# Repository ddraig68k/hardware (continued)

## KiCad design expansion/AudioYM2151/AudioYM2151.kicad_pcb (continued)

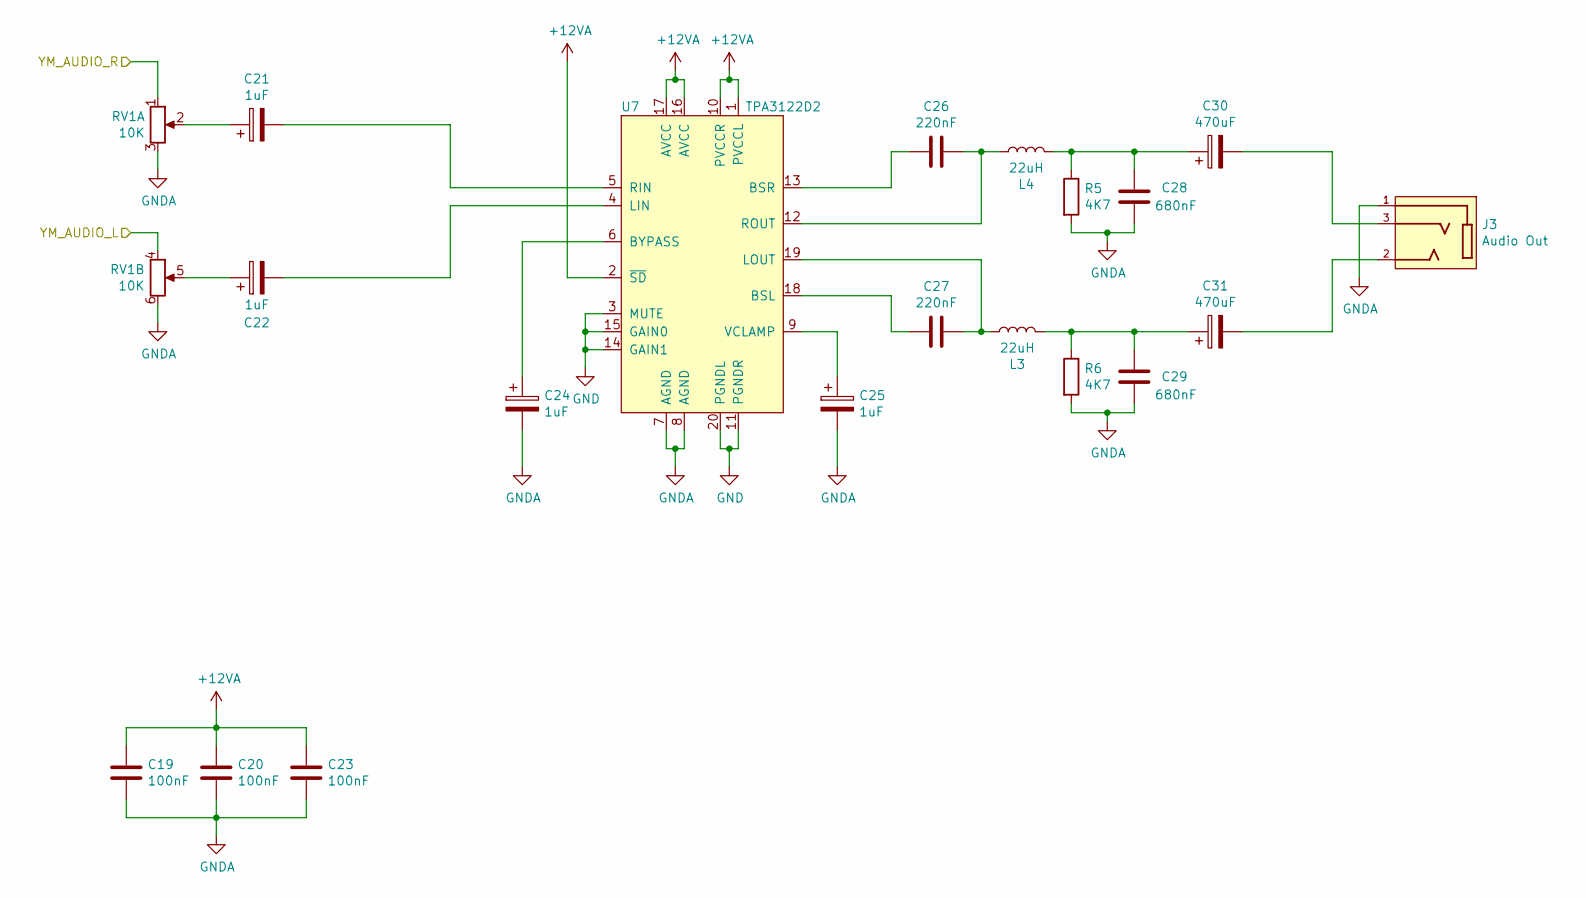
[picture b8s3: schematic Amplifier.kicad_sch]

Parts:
C19, C20, C23: 100nF; C_Disc_D5.0mm_W2.5mm_P2.50mm
C21, C22, C24, C25: 1uF; CP_Radial_D5.0mm_P2.50mm
C26, C27: 220nF; C_Disc_D5.0mm_W2.5mm_P2.50mm
C28, C29: 680nF; C_Disc_D5.0mm_W2.5mm_P2.50mm
C30, C31: 470uF; CP_Radial_D10.0mm_P5.00mm
J3: Audio Out; SWITCHCRAFT_35RAPC2BHN2; PARTREV L
L3, L4: 22uH; L_Radial_D8.7mm_P5.00mm_Fastron_07HCP
R5, R6: 4K7; R_Axial_DIN0207_L6.3mm_D2.5mm_P10.16mm_Horizontal
RV1: 10K; Potentiometer_Alps_RK163_Dual_Horizontal
U7: TPA3122D2; DIP-20_W7.62mm_Socket

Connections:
+12VA: C19.1, C20.1, C23.1, U7.1 (PVCCL), U7.2 (~SD), U7.10 (PVCCR), U7.16 (AVCC), U7.17 (AVCC); also elsewhere on the board
/Amplifier/YM_AUDIO_L: RV1.4; also elsewhere on the board
/Amplifier/YM_AUDIO_R: RV1.1; also elsewhere on the board
GND: U7.3 (MUTE), U7.11 (PGNDR), U7.14 (GAIN1), U7.15 (GAIN0), U7.20 (PGNDL); also elsewhere on the board
GNDA: C19.2, C20.2, C23.2, C24.2, C25.2, C28.1, C29.1, J3.1, R5.2, R6.2, RV1.3, RV1.6, U7.7 (AGND), U7.8 (AGND); also elsewhere on the board
unnamed: C21.1, RV1.2
unnamed: C22.1, RV1.5
unnamed: C28.2, C30.1, L4.2, R5.1
unnamed: C29.2, C31.1, L3.2, R6.1
unnamed: C30.2, J3.3
unnamed: C31.2, J3.2
unnamed: C27.2, U7.18 (BSL)
unnamed: C26.2, U7.13 (BSR)
unnamed: C24.1, U7.6 (BYPASS)
unnamed: C22.2, U7.4 (LIN)
unnamed: C27.1, L3.1, U7.19 (LOUT)
unnamed: C21.2, U7.5 (RIN)
unnamed: C26.1, L4.1, U7.12 (ROUT)
unnamed: C25.1, U7.9 (VCLAMP)

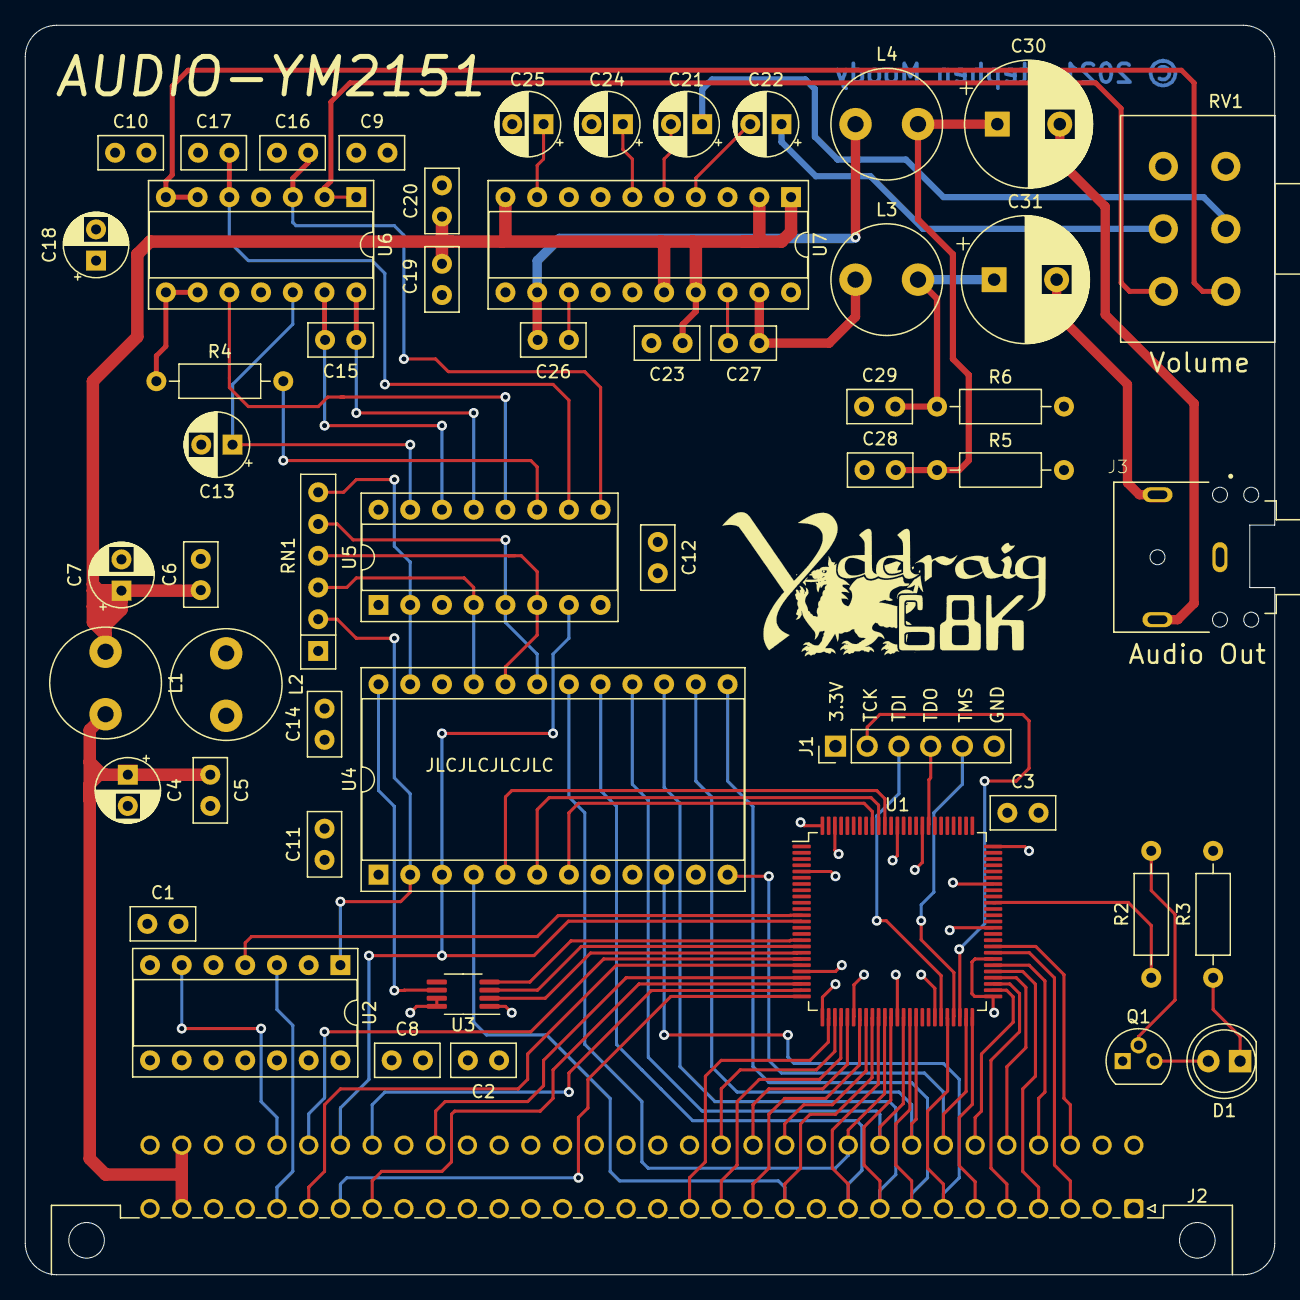
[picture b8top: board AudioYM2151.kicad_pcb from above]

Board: 4 copper layers, 100.0 x 100.0 mm, 54 parts (0 on the bottom side), 83 nets.

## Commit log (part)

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2021-06-23 Added V9990 IC
2021-06-25 Working on V9990 Gfx card
2021-06-25 Added XCA2075M to library
2021-06-25 More additions to the V9990
2021-06-27 Updated YM2612
2021-06-27 Added Eth8019 and updated page description for all projects
2021-06-27 Added extra capacitors to RTL8019
2021-06-27 Started work on V9990 PCB layout
2021-06-29 Updated Mini Din footprints
2021-06-30 Started working on V9958 PCB layout
2021-07-02 Working on YM2612 layout
2021-07-03 Removed V9990 schematic
2021-07-03 Some YM2612 layout changes
2021-07-03 YM2612 layout done
2021-07-05 Done some work on the 68030 design
2021-07-05 Work done on 68K expansion boards
2021-07-06 Removed MSM ADPCM chip from YM2151 board
2021-07-07 Re-started layout on YM2151 board
2021-07-12 Update ddraig logo library symbols
2021-07-13 Started routing Ethernet board
2021-07-13 Finished layout of RTL8019 Ethernet board
2021-07-14 Tidying up logos and copyright
2021-07-22 Re-added V9958 project
2021-07-23 Tiday up of V9958 pcb
2021-07-23 Updated 3D model path reference
2021-07-25 Added joystick board project
2021-07-26 Added PCB for Joypad controller
2021-07-26 Added JTAG labeling on Joypad board
2021-07-27 Changed PCB layout to 100x100 baord
2021-07-28 Updated Trnsistor to SMD part
2021-07-28 Updated v9990 schematic to use SMD parts
2021-07-28 Corrected resistor value from 2K81 -> 2K61
2021-07-29 V9990 part placement done
2021-07-29 Updated PDF schematics for all boards
2021-07-30 Generated gerber files
2021-08-14 Updated incorrectly labeled component
2021-08-18 Completed PCB layout
2021-08-21 Started working on FPGA card design
2021-08-21 More progress on VGA card design
2021-08-21 Started PCB layout
2021-08-23 Improvements on bus wiring pinouts
2021-08-24 Trying to figure out SRAM layout
2021-08-24 Fix for POWER and RESET switches
2021-08-24 Working on the pinning of the FPGA pins
2021-08-25 Updated labeling on Y ddraig board
2021-08-25 Added CPLD code for the Eth8019 card
2021-08-25 Some updates to the VGA FPGA pinout
2021-08-25 Additional work to FPGA VGA schematic
2021-08-26 More work on VGA card
2021-08-28 Changed yddraig68k CPLD macrocells to low power
2021-08-29 Working on YM2203 component
2021-08-29 Added a few extra footprints
2021-08-29 Some minor changes to the FPGA video board
2021-08-29 More work done on the 68030 and 6809 boards
2021-08-29 FIx for 74HCT74 power symbol connections
2021-08-31 Renamed yddraig68k to yddraig
2021-08-31 Updated Readme files
2021-08-31 Some more changes to the 030 and 6809 designs
2021-08-31 Started adding W65C22
2021-09-01 Completed W65C22 part
2021-09-01 Add project names
2021-09-01 changed IC
2021-09-02 Added readme for 6809 board
2021-09-03 Minor changes to DRAM page
2021-09-05 Added RYC8220 to library
2021-09-05 Added IO sheet
2021-09-06 Joypad board, tidied up PCB a little
2021-09-06 TMS9918 - Updated crystal capacitor values to 22pF
2021-09-07 yddraig09 added sd card and iec interfaces
2021-09-07 Updated IO on some of the child sheets
2021-09-08 Buffer for data bus added
2021-09-08 yddraig030 - Updated expansion slot schematics
2021-09-08 Y Ddraig PCB update
2021-09-10 More work y ddraig 030
2021-09-10 More work on yddraig 030
2021-09-11 More 030 changes
2021-09-11 More work on 030 board
2021-09-14 Some work on main ddraig030 sheet
2021-09-14 Changed coaxial connector
2021-09-14 Y Ddraig CPLD code update for PIT
2021-09-14 Yddraig09 Added keyboard page to schematic
2021-09-15 Added some parts for the keyboard controller
2021-09-16 Small updates to keyboard and RAM pages
2021-09-16 More work on 6809 board
2021-09-17 More 6809 changes
2021-09-17 Some tidying up of 6809 project
2021-09-18 ddraig09: Added decode logic and expansion slot
2021-09-18 ddraig09: initial design done
    Need to be reviewed and decode on additional uses for IO but passed DRC
2021-09-19 Asssigned part footprints to most of schematic
2021-09-19 ddraig09: all footprints assigned
2021-09-22 Added initial 6809 board layout design
2021-09-22 Updated the regulator footprint
2021-09-23 Changes to 6809 pcb layout
2021-09-24 Expermienting with 6809 RAM bank logic
2021-09-24 Started removing 6809 sdcard interface
2021-09-26 6809: Restored SD card schematic
2021-09-29 Working on the PCB layout
2021-10-02 ddraig030: Started changing the address decode logic
2021-10-03 ddraig09: Started routing on new layout
2021-10-04 small change
2021-10-06 ddraig030: Some changes to address decoding logic
2021-10-06 ddraig030: Some additional changes to address decoding logic
2021-10-08 Added USB and 72-pin SIMM sockets
2021-10-08 ddraig030: more changes as footprints assigned
2021-10-09 ddraig09: fix for the TSC pin
2021-10-27 Created project for YM2151 CPLD code
2021-10-29 Some basic code for the YM2151 CPLD
2021-11-10 AudioYM2151: Almost done on the CPLD logic, still not working 100%
2021-12-01 yddraig: Updated power circuit to use through hole parts rather than SMD
2021-12-01 yddraig: Moves the DTACK signal from the IRQ line on expansion slot 3
    Close #2
2021-12-01 ym2151: Update to the SPI clock handling code
2021-12-04 ym2151: Added constraints file for the CPLD code
2021-12-05 ym2151: Minor changes and fixed warnings in code
2021-12-06 ym2151: CPLD spi writing seems to be working now
2021-12-06 yddraig030: changed expansion bus and RAM and ROM to 16 bit
2021-12-08 ym2151 CPLD code working correctly
2021-12-10 CPLD for YM2151 made write only, initial YM2612 code
2021-12-13 Added initial V9958 code
2021-12-29 Updated tested cards in readme
2021-12-29 Removed the ddraig030WIP folder
2021-12-30 Updated to KiCAD6
2021-12-30 Spelling fix
2022-01-17 yddraig030: some small changes to the schematic
2022-01-17 Started design for a USB host board
2022-01-17 GfxV9990: Updated CPLD code for the device
2022-02-02 GfxV9990: Changes to the CPLD read and write timings
2022-02-05 JoypadController: Added initial CPLD code
2022-04-08 Updating the YM2151 CPLD codew
2022-04-08 Updated Joypad CPLD to use correct expansion ID
2022-05-07 Updated Joystick controller CPLD code
2022-05-29 Fix for CXA PAL issue and more
2022-06-03 Updated library to new format
2022-06-03 More progress on Spartan-3 FPGA board
2022-06-04 Part placement on video card
2022-06-06 Latest changes to GfxFPGAS3
2022-06-08 Reworking FPGA VGA Card Pinout
2022-06-23 Fix clock frequency setting for YM2151
2022-06-23 More work on the 030 board
2022-06-26 Updated 030 design files
2022-07-29 Added labels to VDP FPGA card
2022-07-29 More changes to the 030 board
2022-07-30 ddraig030 schematic done
2022-07-31 Small changes to 030 design
2022-08-04 More changes in yddraig030 layout
2022-08-10 yddraig030: board changed, ready for footprint assignment
2022-08-10 Some small PCB change?
2022-08-12 Working on PCB layout
2022-08-17 Some more changes to SMD version
2022-08-17 Minor layout changes
2022-08-17 GfxFPGAS3: Added gerber files
2022-08-29 030 board, expansion cards fully routed
2022-08-31 Additional routing don CPU
2022-09-01 Additional routing
2022-09-04 Fix for BUSENABLE not placable on FPGA
2022-09-04 More routing on the 030 board
2022-09-06 More routing
2022-09-08 Board fully routed
2022-09-09 Maybe a final board design?
2022-09-10 Updated silscreen for board
2022-09-10 Updated Yddraig030 schematic
2022-09-10 Updated yddraig09 silkscreen
2022-12-02 Updated readme file
2022-12-02 Added YM2151 picture
2022-12-02 Added y Ddraig image
2022-12-02 Added README to the YM2151
2022-12-02 Updated YM2151 YouTube link
2022-12-02 Mod to YM2151 README
2022-12-03 Added TMS9918 Images
2022-12-03 Added readme for the TMS9918
2022-12-03 Added images for the V9958
2022-12-03 Added README for V9958
2022-12-03 Added README for the V9990
2023-01-14 Updated Logic ICs to specific SMD parts and footprints in schematic
2023-01-14 Updated yddraig030 PCB layout to match schematic changes
2023-01-27 Considering adding second sound channel to 6809 board
2023-01-28 Changes to 030 design completed
2023-02-04 Small updates to 6809 and 030 board, remove old files
2023-02-04 Updated 030 and 6809 gerbers
2023-02-05 Changed a footprint and gerbers for yddraig030
2023-02-06 Updated gerbers with missing bottom solder mask
2023-02-25 Updated 6809 readme
2023-05-20 Updated 68030 CPLD decode logic
2023-07-24 Starting to work on some new boards
2023-07-24 Some updates
2023-09-09 Initial version of a Dual SID audio card
2023-09-09 Removed 74LS125 from schematic
2023-09-16 Changed oscillator frequency on the keyboard controller
2023-09-16 Wotking on SID audio PCB placement
2023-09-17 Working on SID PCB layout
2023-09-18 Audio SID board routed
2023-10-23 Added some labels to Audio SID board
2023-11-15 Working on some new GFX ideas
2023-11-22 Added Spartan-7 FPGA
2023-11-22 Working on HDMI board
2023-11-28 More work on the HDMI board
2024-01-05 Added gerbers to SID board
2024-01-12 Updated AudioSID CPLD code
2024-01-20 FDC updated to KiCAD 7
2024-01-20 All projects updated to KiCAD 7 format files
2024-01-20 Added WIP Boards
2024-01-24 Fixed STACK logic
2024-01-25 Fix for SID Audio VHDL
2024-02-05 Modified volume control on YM2151 card
2024-02-08 Working on CPU schematic
2024-02-09 more work on 68008
2024-02-09 more work on new audio card
2024-02-11 Updated YM2151 Board
2024-02-17 Fix the serial port on yddraig09
2024-02-17 More changes to YM2151V2
2024-02-17 Addon card for yddraig09 to fix bad serial design
2024-02-17 Completed YM2151V2 schematic
2024-02-17 Updated headphone socket cad
2024-02-24 Removed on of the MSM ICs from YM2161V2 design
2024-02-25 Starting pcb layout
2024-02-26 Added more layout changes to new YM2151 board
2024-02-27 Added some CAD models
2024-02-27 Updated 3d models
2024-02-27 Working on footprint positions
2024-02-29 Finished YM2151 audio layout
2024-03-02 Some YM2151 updates
2024-03-02 Started layout of YM2151
2024-03-08 YM2151 board layout progress
2024-03-09 Finished YM2151 board layout
2024-03-25 Initial dram controller code
2024-03-25 DRAM controller compiles
2024-03-29 Updated 030 dram contoller code
2024-03-30 Added some labels to YM2151 V2 board
2024-03-30 Updated DRAM test bench
2024-05-16 Some changes to YM2151 V2 Board
2024-05-17 Updated YM2151V2 crystal capacitors to 15pf
2024-05-17 Latest changes
2024-05-17 Updated libraries with the latest additions
2024-05-17 ddraig030: Updated some 3d models on the PCB layout
2024-05-17 yddraig: Updated some 3d models on the PCB layout and altered CPLD DRAM timing
2024-05-17 V9990 card, restored some timing from the V9990 CPLD
2024-05-17 AudioSID: Fix to CPLD decode logic
2024-05-17 Fixed some AudioYM2151V2 DRC issues
2024-05-17 Added additional user LED to YM2151V2 design
2024-05-24 Looking at working on new FPGA video card
2024-05-24 Genereted YM2151V2 gerber files
2024-05-25 Pinout done one VGA card
2024-05-25 intitial FPGA routing done
2024-05-26 Added 32 bit version of VGA card
2024-06-01 Fixed DTACK signal generation
2024-06-05 V9990 WIP
2024-06-06 Some changed to track limits for FPGA board
2024-06-07 Updating YM2151V2 readme
2024-06-07 Fixed the DUART on the 6809
2024-06-12 Saved in V8 format
2024-06-24 Working on VGA baord layout
2024-06-24 VGA board v2 routing done
2024-07-11 WOrking on FPGA VGA board
2024-07-12 WOrking on VGA card
2024-07-13 Finished FPGA board layout
2024-07-19 Updated V9990 schematic
2024-07-19 Some changes
2024-07-21 Changing the yddraig09 project
2024-07-27 6809 board changes
2024-07-27 Gfx FPGA and V9990 gerber changes
2024-07-28 Changes to yddraig09
2024-07-30 More changes
2024-07-31 Changed RTC
2024-08-03 Changed RTC and board layout
2024-08-04 Updated V9990 and FPGA board
2024-08-14 BOard changes
2024-08-28 Added gerber files got VGA and V9990 cards
2024-09-09 Updated Audio socket on V9990 board
2024-10-01 V9990 and VGA Minor updates and new gerbers
2024-10-13 Updated 030 address decode logic
2024-10-17 Changing v9990 board
2024-10-19 Changes to the HDMI board
2025-01-11 Repository clean up, removed untested projects
    Updated files to latest KiCAD version
    Removed untested 68030 design files
    Removed 6809 board, several design flaws
    Removed untested expansion boards
2025-01-11 Update README.md
    Removed KiCAD 6 reference
2025-01-16 Updated MC68681 symbol
2025-10-01 Added the design files for GfxvGA card
2026-02-27 Merged 2 conflicting branches
2026-04-16 Added second clock out to CPLD
2026-04-16 Fixed incorrect pin name
2026-05-22 Added XC7S50 part
2026-05-26 Added missing symbols and CAD files
2026-05-28 Added regulator symbol
